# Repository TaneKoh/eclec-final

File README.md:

I2S digital input

1. DMA moves I2S data to memory

2. I2S half/full interrupt triggers DSP function

3. DSP Math:
a. convert to float
b. biquad filters
c. volume control
d. convert back to int

4. write to output buffer

order of operations approach:

1. hardware bring-up (do blinking LED)

2. do pass-through config (no filtering)

3. config actual DSP

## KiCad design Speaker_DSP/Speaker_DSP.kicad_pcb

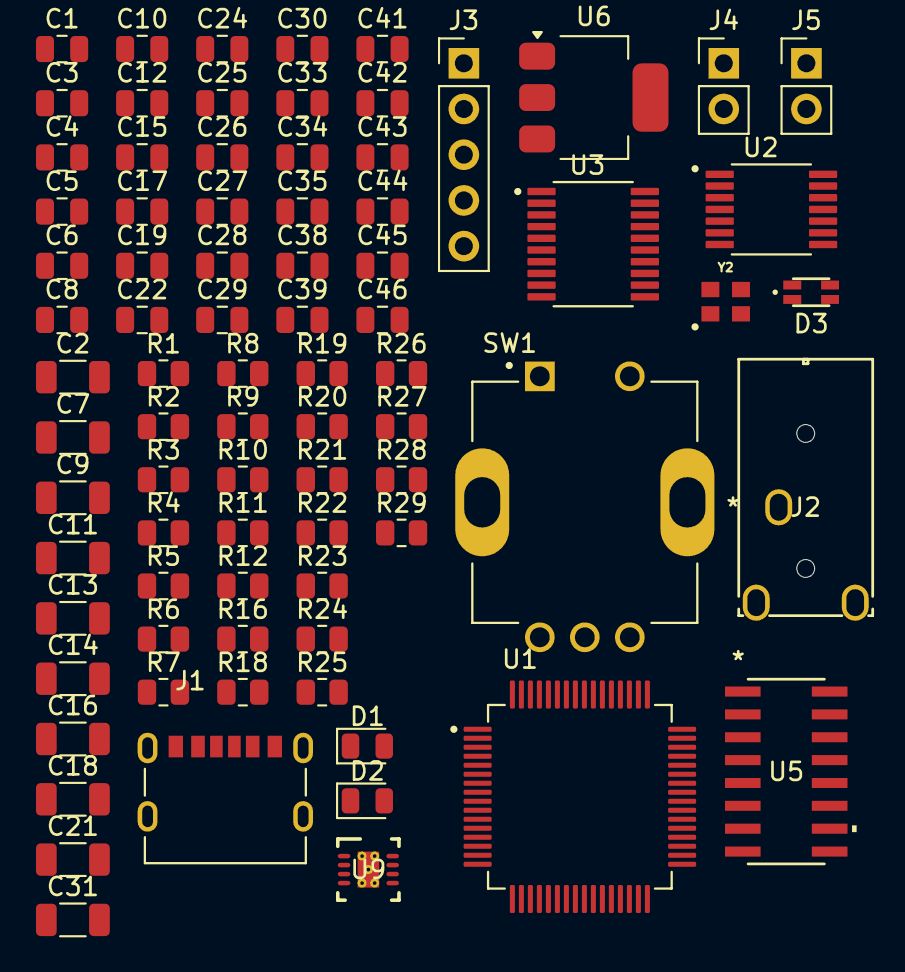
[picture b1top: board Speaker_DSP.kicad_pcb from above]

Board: 2 copper layers, 81 parts (0 on the bottom side), 56 nets, no tracks yet.

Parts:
C1, C6, C8, C10, C12, C15, C17, C29, C30: 0.1 uf; C_0805_2012Metric
C2, C7, C9, C11, C13, C14, C16, C18, C21, C31: 10 uf; C_1206_3216Metric
C3, C34: 100 nf; C_0805_2012Metric
C4, C5, C33: 2.2 uf; C_0805_2012Metric
C19, C22, C24, C25, C38, C46: 1 uf; C_0805_2012Metric
C26, C27, C28: 0.01 uf; C_0805_2012Metric
C35, C43: 2.2 nf; C_0805_2012Metric
C39: 10 uf; C_0805_2012Metric
C41: 1uf; C_0805_2012Metric
C42, C44: 1 nf; C_0805_2012Metric
C45: 1 uF; C_0805_2012Metric
D1: Green PWR; LED_0805_2012Metric
D2: Orange STATUS; LED_0805_2012Metric
D3: IN-S85TATRGB
J1: USB-C power in; SAMESKY_UJC-H-G-SMT-1-P6-TR
J2: STX-3000; STX-3000_KYC
J3: SWD; PinHeader_1x05_P2.54mm_Vertical
J4, J5: Conn_01x02; PinHeader_1x02_P2.54mm_Vertical
R1, R2, R3, R4, R5, R6, R16, R18, R21, R22: 10k; R_0805_2012Metric
R7, R8, R28: 5.1k; R_0805_2012Metric
R9: 10 k; R_0805_2012Metric
R10: 10k ohm; R_0805_2012Metric
R11, R12: 100; R_0805_2012Metric
R19, R20, R23, R24, R25, R26, R27, R29: 1k; R_0805_2012Metric
SW1: PEC11R-4215F-S0024; XDCR_PEC11R-4215F-S0024
U1: STM32F446RET6TR; QFP50P1200X1200X160-64N
U2: PCM1808PWR; SOP65P640X120-14N
U3: PCM5102APWR; SOP65P640X120-20N
U5: PAM8406DR; SO-16_PAM8406_DIO
U6: AMS1117-3.3; SOT-223-3_TabPin2
U9: OPA1678IDRGT; DRG0008A
Y2: 8MHz 831072801; WE-SPXO_IQXO-791

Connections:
+3.3V: C1.1, C2.1, C6.2, C7.2, C8.1, C9.1, C16.1, C17.1, C18.1, C29.1, C30.1, C31.1, C34.1, D3.3, J3.1, R1.1, R3.1, R5.1, R25.2, U1.1 (VBAT), U1.13 (VDDA/VREF+), U1.19 (VDD), U1.32 (VDD), U1.48 (VDD), U1.64 (VDD), U2.4 (VDD), U3.1 (CPVDD), U3.8 (AVDD), U3.17 (XSMT), U3.20 (DVDD), U6.2 (VO), Y2.1 (E/D), Y2.4 (+VS)
+5V: C14.2, C15.2, C19.1, C21.1, C22.1, C39.1, C46.1, J1.A9 (VBUS), J1.B9 (VBUS), R16.2, R22.2, U2.3 (VCC), U5.4 (PVDDL), U5.5 (*MUTE), U5.6 (VDD), U5.9 (MODE), U5.12 (*SHND), U5.13 (PVDDR), U6.3 (VI), U9.8 (V+)
/LED_B: R29.2, U1.39 (PC8/TRACED0/TIM3_CH3/TIM8_CH3/UART5_RTS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)
/LED_G: R28.2, U1.38 (PC7/TIM3_CH2/TIM8_CH2/FMPI2C1_SDA/SPI2_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)
/LED_R: R27.2, U1.37 (PC6/TIM3_CH1/TIM8_CH1/FMPI2C1_SCL/I2S2_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)
GND: C1.2, C2.2, C3.2, C4.2, C6.1, C7.1, C8.2, C9.2, C10.2, C11.2, C12.1, C13.1, C14.1, C15.1, C16.2, C17.2, C18.2, C19.2, C21.2, C22.2, C26.2, C27.2, C28.2, C29.2, C30.2, C31.2, C33.2, C34.2, C38.2, C39.2, C42.2, C44.1, C46.2, D1.1 (K), D2.1 (K), J1.A12 (GND), J1.B12 (GND), J1.SH1 (SHIELD), J1.SH2 (SHIELD), J1.SH3 (SHIELD), J1.SH4 (SHIELD), J3.4, R7.2, R8.2, R9.1, R10.1, R18.1, R21.1, SW1.1, SW1.COM, SW1.S1 (SHIELD), SW1.S2 (SHIELD__1), U1.12 (VSSA/VREF-), U1.18 (VSS), U1.31 (VSS), U1.47 (VSS), U1.63 (VSS), U2.2 (AGND), U2.5 (DGND), U2.10 (MD0), U2.11 (MD1), U2.12 (FMT), U3.3 (CPGND), U3.9 (AGND), U3.10 (DEMP), U3.11 (FLT), U3.16 (FMT), U3.19 (DGND), U5.2 (PGNDL), U5.11 (GND), U5.15 (PGNDR), U6.1 (GND), U9.4 (V-), U9.9 (PAD), Y2.2 (GND)
unnamed: C24.2, R16.1, R18.2, R19.2
unnamed: C25.2, R21.2, R22.1, R23.2
unnamed: C35.2, R19.1, R20.2
unnamed: C43.2, R23.1, R24.2
unnamed: D1.2 (A), R25.1
unnamed: D2.2 (A), R26.2
unnamed: D3.1, R27.1
unnamed: D3.2, R28.1
unnamed: D3.4, R29.1
unnamed: J1.A5 (CC1), R7.1
unnamed: J1.B5 (CC2), R8.1
unnamed: J3.2, U1.49 (PA14/JTCK-SWCLK/EVENTOUT)
unnamed: J3.3, U1.46 (PA13/JTMS-SWDIO/EVENTOUT)
unnamed: C3.1, J3.5, U1.7 (NRST)
unnamed: J4.1, U5.1 (+OUT_L)
unnamed: J4.2, U5.3 (-OUT_L)
unnamed: J5.1, U5.16 (+OUT_R)
unnamed: J5.2, U5.14 (-OUT_R)
unnamed: R1.2, R2.1, SW1.2
unnamed: R3.2, R4.1, SW1.A
unnamed: R5.2, R6.1, SW1.B
unnamed: R10.2, U1.60 (BOOT0)
unnamed: U1.20 (PA4/SPI1_NSS/I2S1_WS/SPI3_NSS/I2S3_WS/U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), U2.7 (LRCK), U3.15 (LRCK)
unnamed: R26.1, U1.21 (PA5/TIM2_CH1/TIM2_ETR/TIM8_CH1N/SPI1_SC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)
unnamed: U1.22 (PA6/TIM1_BKIN/TIM3_CH1/TIM8_BKIN/SPI1_M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), U2.6 (SCKI), U3.12 (SCK)
unnamed: R9.2, U1.28 (PB2-BOOT1(PB2)/TIM2_CH4/SAI1_SD_A/SPI3_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)
unnamed: C26.1, R2.2, U1.57 (PB5/TIM3_CH2/I2C1_SMBA/SPI1_MOSI/I2S1_S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)
unnamed: C27.1, R4.2, U1.58 (PB6/TIM4_CH1/HDMI_CEC/I2C1_SCL/USART1_T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)
unnamed: C28.1, R6.2, U1.59 (PB7/TIM4_CH2/I2C1_SDA/USART1_RX/SPDIFRX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)
unnamed: U1.36 (PB15/RTC_REFIN/TIM1_CH3N/TIM8_CH3N/SPI2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), U3.14 (DIN)
unnamed: U1.51 (PC10/SPI3_SCK/I2S3_CK/USART3_TX/UART4_T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), U2.8 (BCK), U3.13 (BCK)
unnamed: U1.53 (PC12/I2C2_SDA/SPI3_MOSI/I2S3_SD/USART3_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), U2.9 (DOUT)
unnamed: U1.5 (PH0-OSC_IN/EVENTOUT), Y2.3 (OUT)
unnamed: C33.1, U1.30 (VCAP_1)
unnamed: R12.1, U2.13 (VINL)
unnamed: R11.2, U2.14 (VINR)
unnamed: C12.2, C13.2, U2.1 (VREF)
unnamed: C5.1, U3.4 (CAPM)
unnamed: C5.2, U3.2 (CAPP)
unnamed: C10.1, C11.1, U3.18 (LDOO)
unnamed: C41.1, U3.6 (OUTL)
unnamed: C45.1, U3.7 (OUTR)
unnamed: C4.1, U3.5 (VNEG)
unnamed: C41.2, U5.7 (INL)
unnamed: C45.2, U5.10 (INR)
unnamed: C38.1, U5.8 (VREF)
unnamed: C42.1, R20.1, U9.3 (IN+)
unnamed: C35.1, R12.2, U9.1 (OUT), U9.2 (IN-)
unnamed: C44.2, R24.1, U9.5 (IN+)
unnamed: C43.1, R11.1, U9.6 (IN-), U9.7 (OUT)
